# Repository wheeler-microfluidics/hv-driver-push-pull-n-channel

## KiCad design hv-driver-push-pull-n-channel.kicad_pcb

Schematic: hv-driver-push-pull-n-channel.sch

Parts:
C1: 0.1uF; C_1206
C2: 0.1uF; C_1210
C3: C; C_1210
D1, D2: D; SMA_Standard
F1: FUSE; Resistor_Vertical_RM5mm
P1: CONN_01X04; Pin_Header_Straight_1x04
P2: CONN_01X03; Pin_Header_Straight_1x03
Q1, Q2: Q_NMOS_GDS; TO-220_Neutral123_Vertical
R1: 10; R_1206
R4: R; R_1206
U1: NCP5304; SOIC-8-N

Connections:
GND: C1.1, D2.2 (A), P1.2, P2.3, Q2.3, R4.2, U1.4 (GND)
HV: P2.1, Q1.2
IN_HI: P1.4, U1.2 (IN_HI)
IN_LO: P1.3, U1.1 (IN_LO)
unnamed: C2.1, D2.1 (K), R1.2, U1.6 (BRIDGE)
unnamed: C2.2, D1.1 (K), U1.8 (VBOOT)
unnamed: C3.1, Q1.3, Q2.2, R1.1
unnamed: F1.2, P2.2
unnamed: Q1.1, U1.7 (DRV_HI)
unnamed: Q2.1, U1.5 (DRV_LO)
OUT: C3.2, F1.1, R4.1
VCC: C1.2, D1.2 (A), P1.1, U1.3 (VCC)

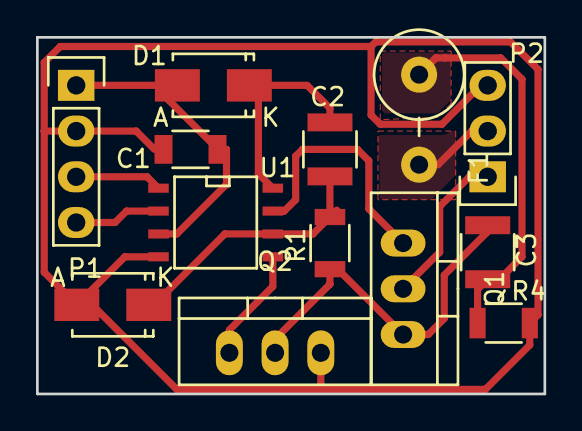
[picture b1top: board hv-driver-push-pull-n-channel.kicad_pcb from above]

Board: 2 copper layers, 28.2 x 19.8 mm, 13 parts (0 on the bottom side), 12 nets.

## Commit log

2016-04-14 Add negative voltage protection
2016-04-14 Put header pins on 0.1in grid
2016-04-14 Make compatible with CNC milling
2016-04-25 Change length to match main board and add fuse
2016-05-11 Use T220 transistors and add gate resistors
2016-05-11 Remove gate resistors
2017-04-04 Add svg, png, pdf outputs
2017-07-13 added appveyor.yml
2017-07-14 AppVeyor Configuration Updated
2017-07-18 AppVeyor Update: "a4e909ac7a44d2708564d46a9b978b95c8367686"
2017-07-19 AppVeyor Update: "d5d159050eac48ab9123f383fe8e949476d7f60f"
2017-07-20 AppVeyor Update: "35852f667457a927c170bb71278740b12d7a8f75"
